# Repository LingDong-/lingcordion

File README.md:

# Lingcordion

A pocket-sized digital musical instrument inspired by the piano and the accordion.

This repo hosts the design files of the PCB, source code for the firmware, and CAD parts for 3D printing.

## Features

- 3 playable octaves on the right hand, bass/chord mode on the left hand.
- On-board synthesizer / MIDI output (USB).
- On-board speaker / 3.5mm audio jack.
- Easy to learn, fits in your back pocket.

## How to Play

[Here's a video of me playing the instrument.](doc/v01.mp4)

https://github.com/user-attachments/assets/264b68fd-24f3-4782-8792-03d39f5a074a

- The index, middle, ring and (optionally) pinky fingers go between the strap and the palm rest, to play note keys on the front side.
- The thumbs press and hold modifier keys on the back side.

## BOM

- 28 limit switches
- ESP32-S3 module with more than 4 MB of flash
- LM4871 for audio power amplifier
- MCP4921 for DAC
- Assorted 1206 resistors capacitors. Misc. buttons and switches. 1117 3.3V regulator.

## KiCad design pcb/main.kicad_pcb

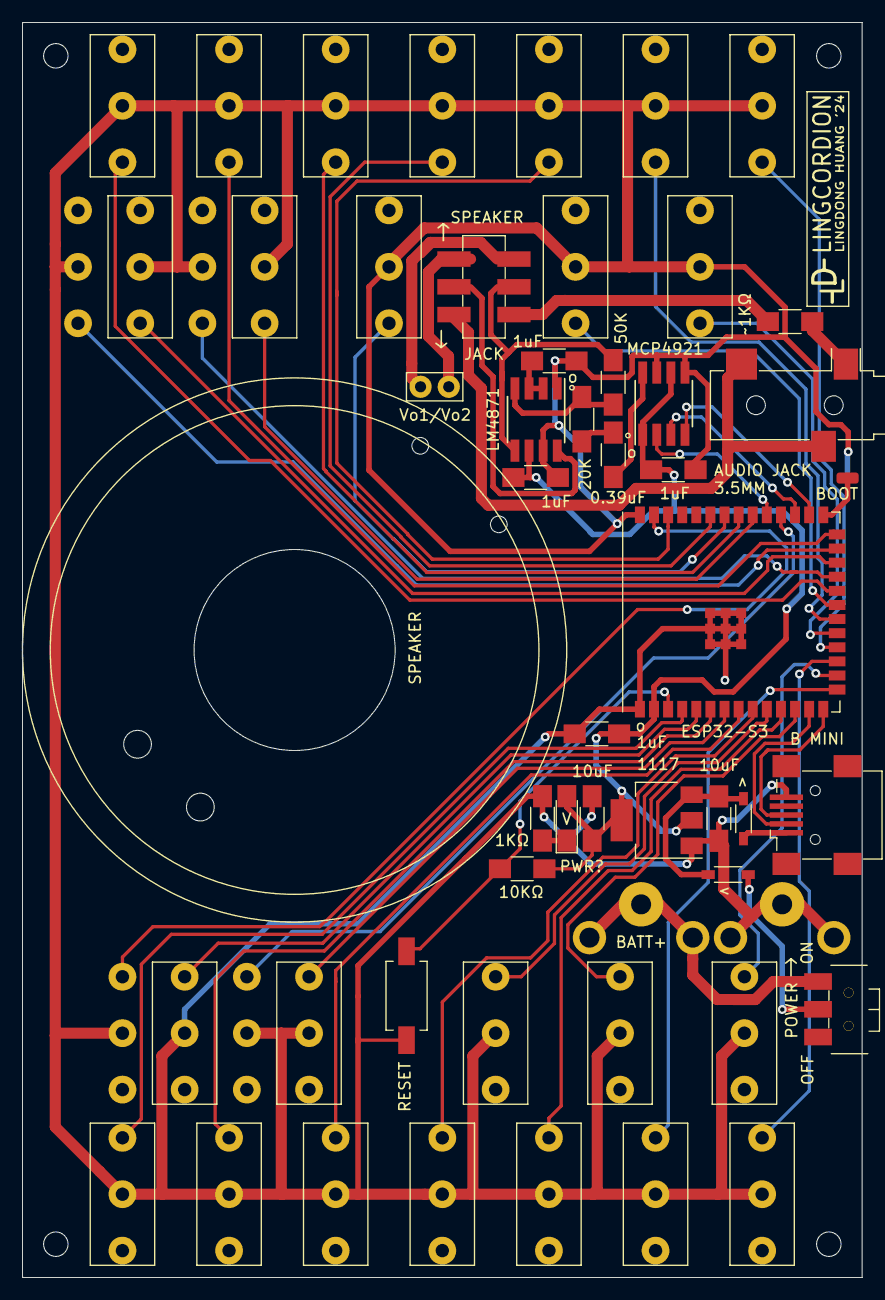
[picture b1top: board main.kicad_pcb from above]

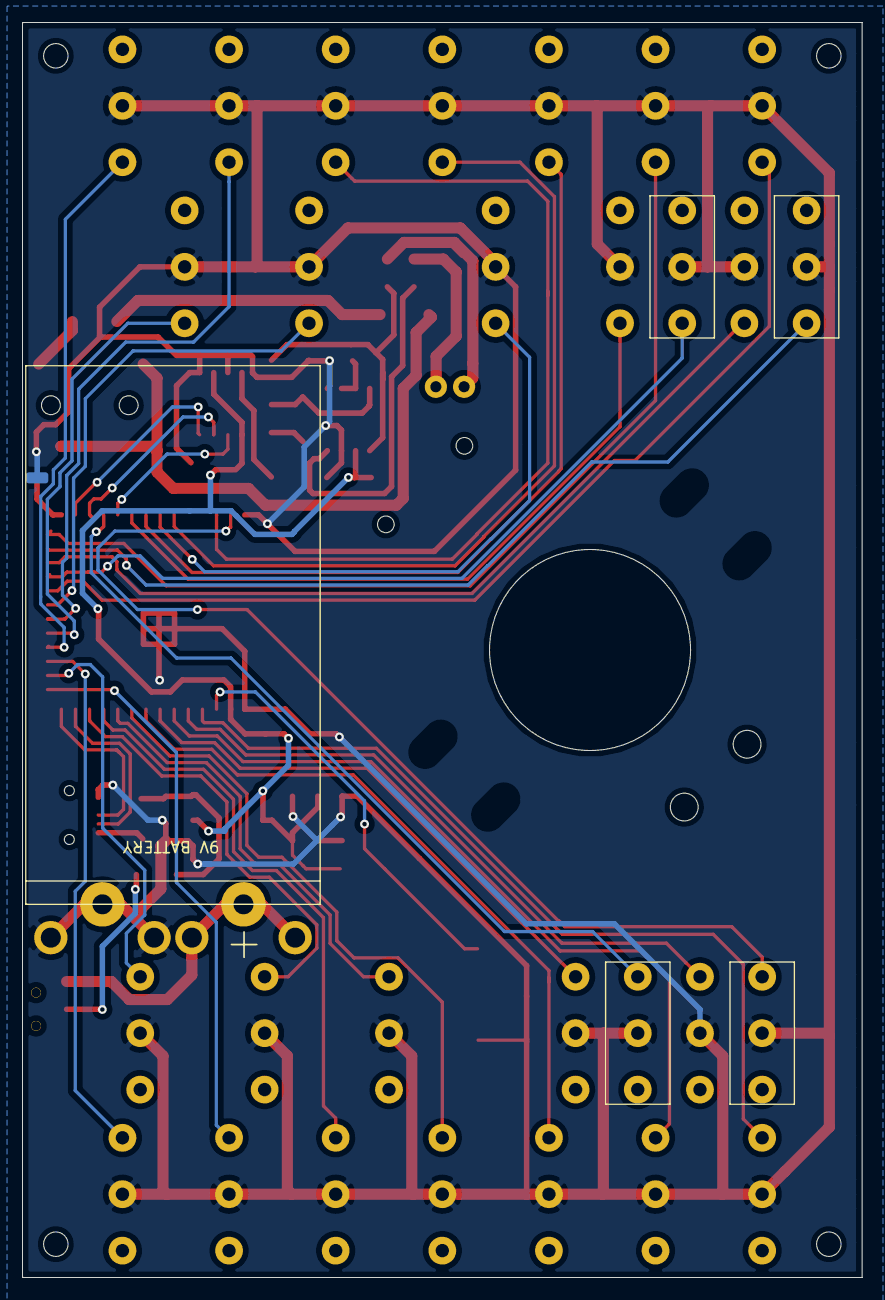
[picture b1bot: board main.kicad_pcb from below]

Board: 2 copper layers, 75.6 x 113.0 mm, 61 parts (6 on the bottom side), 53 nets.

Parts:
BT1: Battery_Cell; 9V_CONTACT_ON_BRD
C1, C2, C3, C7: C; C_1206
C4: C0.39uF; C_1206
C5, C6: C1uF; C_1206
D1, D2: D_Schottky; SOD-123
D3: LED; LED_1206
H1: MountingHole; SPEAKER_MOUNT
H2, H3, H4, H5: MountingHole; MountingHole_2.2mm_M2
J1, J7: Conn_01x01; SolderWirePad_1x01_SMD_1x2mm
J2: Conn_PinHeader_1x02_P2.54mm_Vertical_THT_D1mm; PinHeader_1x02_P2.54mm_Vertical_THT_D1mm
J3: USB_B_Mini; USB_Mini-B_Wuerth_65100516121_Horizontal
J6: AudioJack2_Ground; Jack_3.5mm_CUI_SJ-3523-SMT_Horizontal
R1, R2, R10: R; R_1206
R3, R4: R20K; R_1206
SW1: BUTTON_PTS636; Button_C&K_PTS636_6x3.5mm
SW2: SWITCH_AYZ0102AGRLC; Switch_SPDT_C&K_AYZ0102AGRLC_7.2x3mm_P2.5mm
SW3: SW_Push_DPDT; SW_DPDT_CK_JS202011JCQN
SW4, SW5, SW6, SW7, SW8, SW9, SW10, SW11, SW12, SW13, SW14, SW15, SW16, SW17, SW18, SW19, SW20, SW21, SW22, SW23, SW24, SW25, SW26, SW27, SW28, SW29, SW30, SW31: SW_SPDT; LIMIT_SWITCH_TE_SAJ
U1: Regulator_Linear_ZLDO1117-3.3V-1A; SOT-223-3_TabPin2
U2: ESP32-S3-WROOM-1
U3: AMP_MONO_LM4871M; SOIC-8_3.9x4.9mm_P1.27mm
U4: MCP4901; SOIC-8_3.9x4.9mm_P1.27mm

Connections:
+3V3: C1.1, C3.1, C6.1, C7.1, D3.2, R1.1, U1.2, U2.2, U3.6, U4.1, U4.6
+5V: D1.2, J3.1
+BATT: BT1.2, SW2.3
/Audio_Input: C4.2, U4.8
/CS_DAC: U2.31, U4.2
/HdVo1: R10.1, SW3.3
/HdVo2: J6.R, J6.T, SW3.6
/IO1: SW28.2, U2.39
/IO2: SW20.2, U2.38
/IO3: SW13.2, U2.15
/IO4: SW4.2, U2.4
/IO5: SW5.2, U2.5
/IO6: SW6.2, U2.6
/IO7: SW7.2, U2.7
/IO8: SW12.2, U2.12
/IO9: SW15.2, U2.17
/IO10: SW16.2, U2.18
/IO11: SW17.2, U2.19
/IO12: SW18.2, U2.20
/IO13: SW19.2, U2.21
/IO14: SW27.2, U2.22
/IO15: SW8.2, U2.8
/IO16: SW9.2, U2.9
/IO17: SW10.2, U2.10
/IO18: SW11.2, U2.11
/IO21: SW30.2, U2.23
/IO39: SW24.2, U2.32
/IO40: SW23.2, U2.33
/IO41: SW22.2, U2.34
/IO42: SW21.2, U2.35
/IO45: SW25.2, U2.26
/IO46: SW14.2, U2.16
/IO47: SW26.2, U2.24
/IO48: SW31.2, U2.25
/MISO: SW29.2, U2.30
/MOSI: U2.28, U4.4
/SCK: U2.29, U4.3
/SpVo1: J2.1, SW3.1
/SpVo2: J2.2, SW3.4
/Vo1: R4.2, SW3.2, U3.5
/Vo2: SW3.5, U3.8
GND: BT1.1, C1.2, C2.2, C3.2, C5.2, C6.2, C7.2, J3.5, J7.1, R2.1, SW1.1, SW4.3, SW5.3, SW6.3, SW7.3, SW8.3, SW9.3, SW10.3, SW11.3, SW12.3, SW13.3, SW14.3, SW15.3, SW16.3, SW17.3, SW18.3, SW19.3, SW20.3, SW21.3, SW22.3, SW23.3, SW24.3, SW25.3, SW26.3, SW27.3, SW28.3, SW29.3, SW30.3, SW31.3, U1.1, U2.1, U2.40, U2.41, U3.1, U3.7, U4.5, U4.7
unnamed: C2.1, D1.1, D2.1, U1.3
unnamed: C4.1, R3.2
unnamed: C5.1, U3.2, U3.3
unnamed: D2.2, SW2.2
unnamed: D3.1, R2.2
unnamed: J1.1, U2.27
unnamed: J3.2, U2.13
unnamed: J3.3, U2.14
unnamed: J6.S, R10.2
unnamed: R1.2, SW1.2, U2.3
unnamed: R3.1, R4.1, U3.4
